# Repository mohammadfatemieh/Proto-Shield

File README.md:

# Proto-Shield
Prototyping Shield for Arduino.

* Open-Source and released under the [Creative Commons Attribution Share-Alike License](https://creativecommons.org/licenses/by-sa/4.0/).
* **[Documentation on learn.watterott.com](https://learn.watterott.com)**

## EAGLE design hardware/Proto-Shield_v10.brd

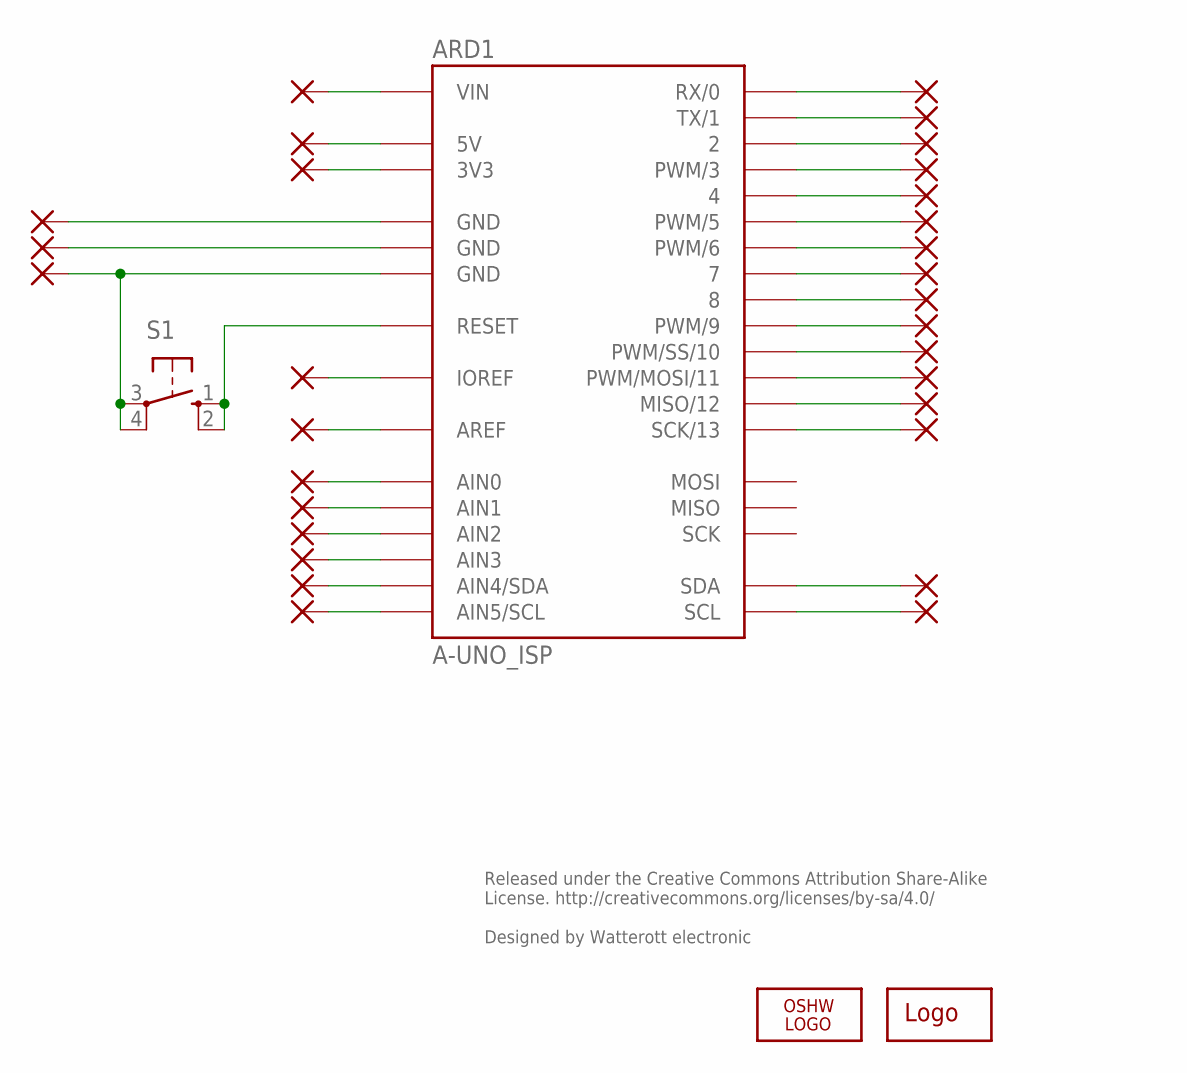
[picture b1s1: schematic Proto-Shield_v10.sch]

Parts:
ARD1: A-UNO_ISP; A-UNO-ISP
LOGO1: OSHW_LOGOX0070; OSHW_6X70
LOGO2: LOGO-S_PLACE_S; SPARK_TPLACE_S
PAD1, PAD2, PAD3, PAD4, PAD5, PAD6, PAD7, PAD8, PAD9, PAD10, PAD11, PAD12, PAD13, PAD14, PAD15, PAD16, PAD17, PAD18, PAD19, PAD20, PAD21, PAD22, PAD23, PAD24, PAD25, PAD26, PAD27, PAD28, PAD29, PAD30: 1,6/0,9
S1: 10-XX; B3F-10XX

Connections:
unnamed: ARD1.RST (RESET), S1.1 (S), S1.2 (S1)
unnamed: ARD1.IOREF, PAD24.1
unnamed: ARD1.AREF, PAD23.1
unnamed: ARD1.A0 (AIN0), PAD17.1
unnamed: ARD1.A1 (AIN1), PAD18.1
unnamed: ARD1.A2 (AIN2), PAD19.1
unnamed: ARD1.A3 (AIN3), PAD20.1
unnamed: ARD1.A4 (AIN4/SDA), PAD21.1
unnamed: ARD1.A5 (AIN5/SCL), PAD22.1
unnamed: ARD1.3V3, PAD28.1
unnamed: ARD1.5V, PAD29.1
unnamed: ARD1.VIN, PAD30.1
unnamed: ARD1.0 (RX/0), PAD1.1
unnamed: ARD1.1 (TX/1), PAD2.1
unnamed: ARD1.2, PAD3.1
unnamed: ARD1.3 (PWM/3), PAD4.1
unnamed: ARD1.4, PAD5.1
unnamed: ARD1.5 (PWM/5), PAD6.1
unnamed: ARD1.6 (PWM/6), PAD7.1
unnamed: ARD1.7, PAD8.1
unnamed: ARD1.8, PAD9.1
unnamed: ARD1.9 (PWM/9), PAD10.1
unnamed: ARD1.10 (PWM/SS/10), PAD11.1
unnamed: ARD1.11 (PWM/MOSI/11), PAD12.1
unnamed: ARD1.12 (MISO/12), PAD13.1
unnamed: ARD1.13 (SCK/13), PAD14.1
unnamed: ARD1.SDA, PAD15.1
unnamed: ARD1.SCL, PAD16.1
unnamed: ARD1.GND@2 (GND), PAD26.1
unnamed: ARD1.GND@1 (GND), PAD27.1
unnamed: ARD1.GND@3 (GND), PAD25.1, S1.3, S1.4 (P1)

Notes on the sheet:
Released under the Creative Commons Attribution Share-Alike License. http://creativecommons.org/licenses/by-sa/4.0/ Designed by Watterott electronic

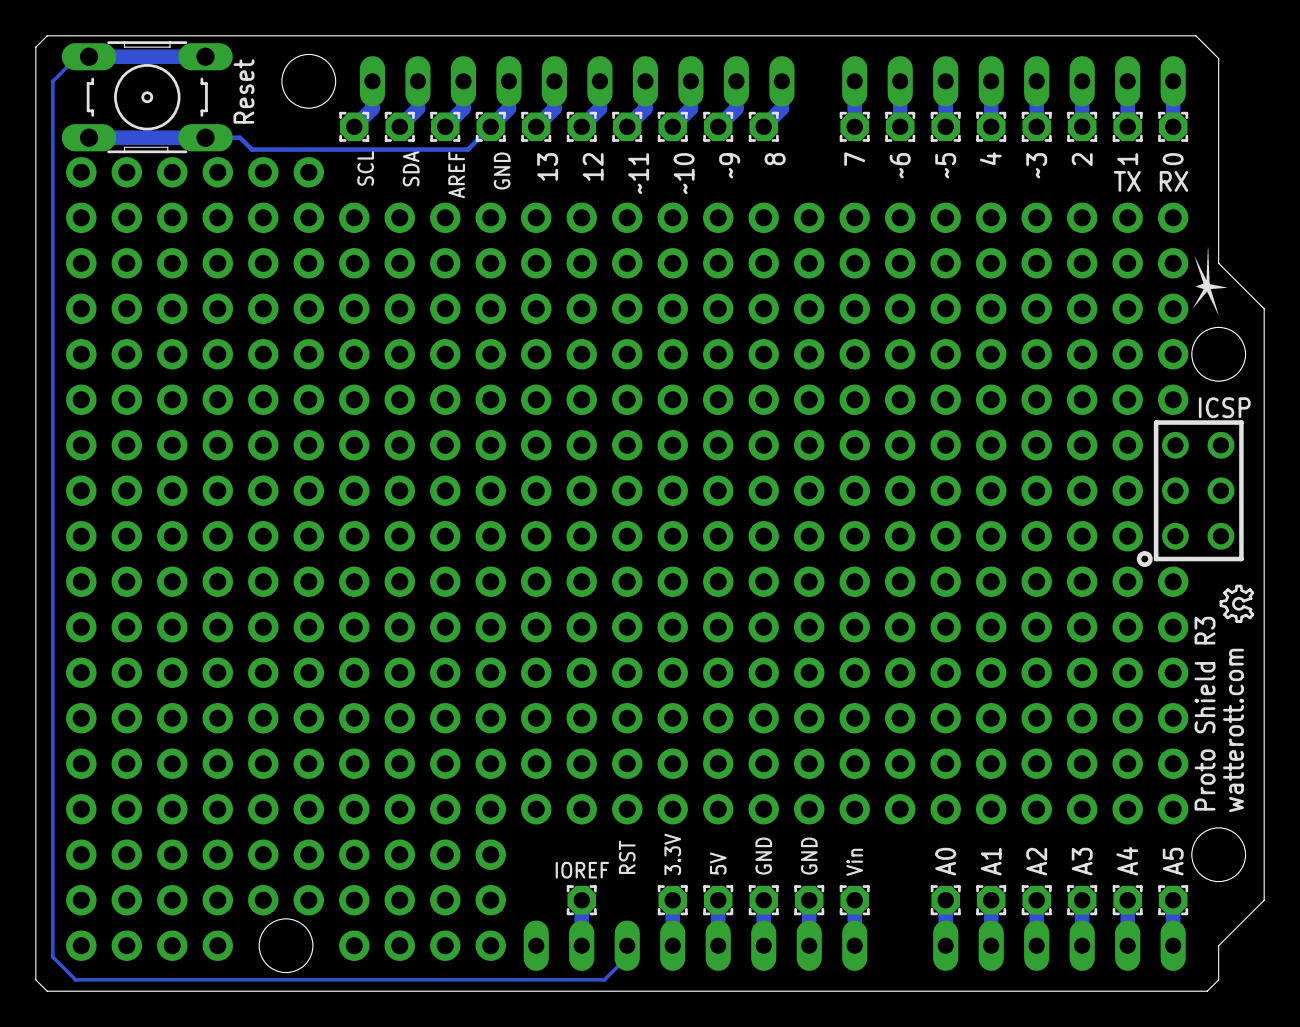
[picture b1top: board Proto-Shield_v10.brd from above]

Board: 2 copper layers, 68.6 x 53.3 mm, 34 parts (0 on the bottom side), 31 nets.
